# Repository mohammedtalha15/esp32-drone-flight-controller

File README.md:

# Custom ESP32 Devboard

It's a custom ESP32 devboard. It was designed to be a drone flight controller, but it's suitable for other projects as well.
I wanted to make this because I thought it was a good idea to try to design a drone with custom electronics. Turns out, electronics are hard, so I just made this.
It'll go on the drone when all the other parts are done. This project is being made for and funded by Hack Club's Highway program. 

This is my first circuit board by the way, hopefully I did a good job. I'm planning on designing my own brushless motor speed controller next, but I may just move on to the drone if that's too hard. 

## Features
- Integrated gyro and accelerometer (MPU-6050)
- Integrated magnetometer
- Voltage Regulator that drops drone battery voltage (14.8v) to 5v
- ESP32 Chip for processing, wifi, and bluetooth connectivity
- USB-C 2.0 port for programming and power supply
- Boot and Reset buttons
- A whole lotta GPIO pins

## BOM

| Item  | Usage | Source  | Price | Quantity |
| ----| ----|----|----|----|
| PCB | This is the project lol | JLCPCB | $77 | 5 (2 assembled)|

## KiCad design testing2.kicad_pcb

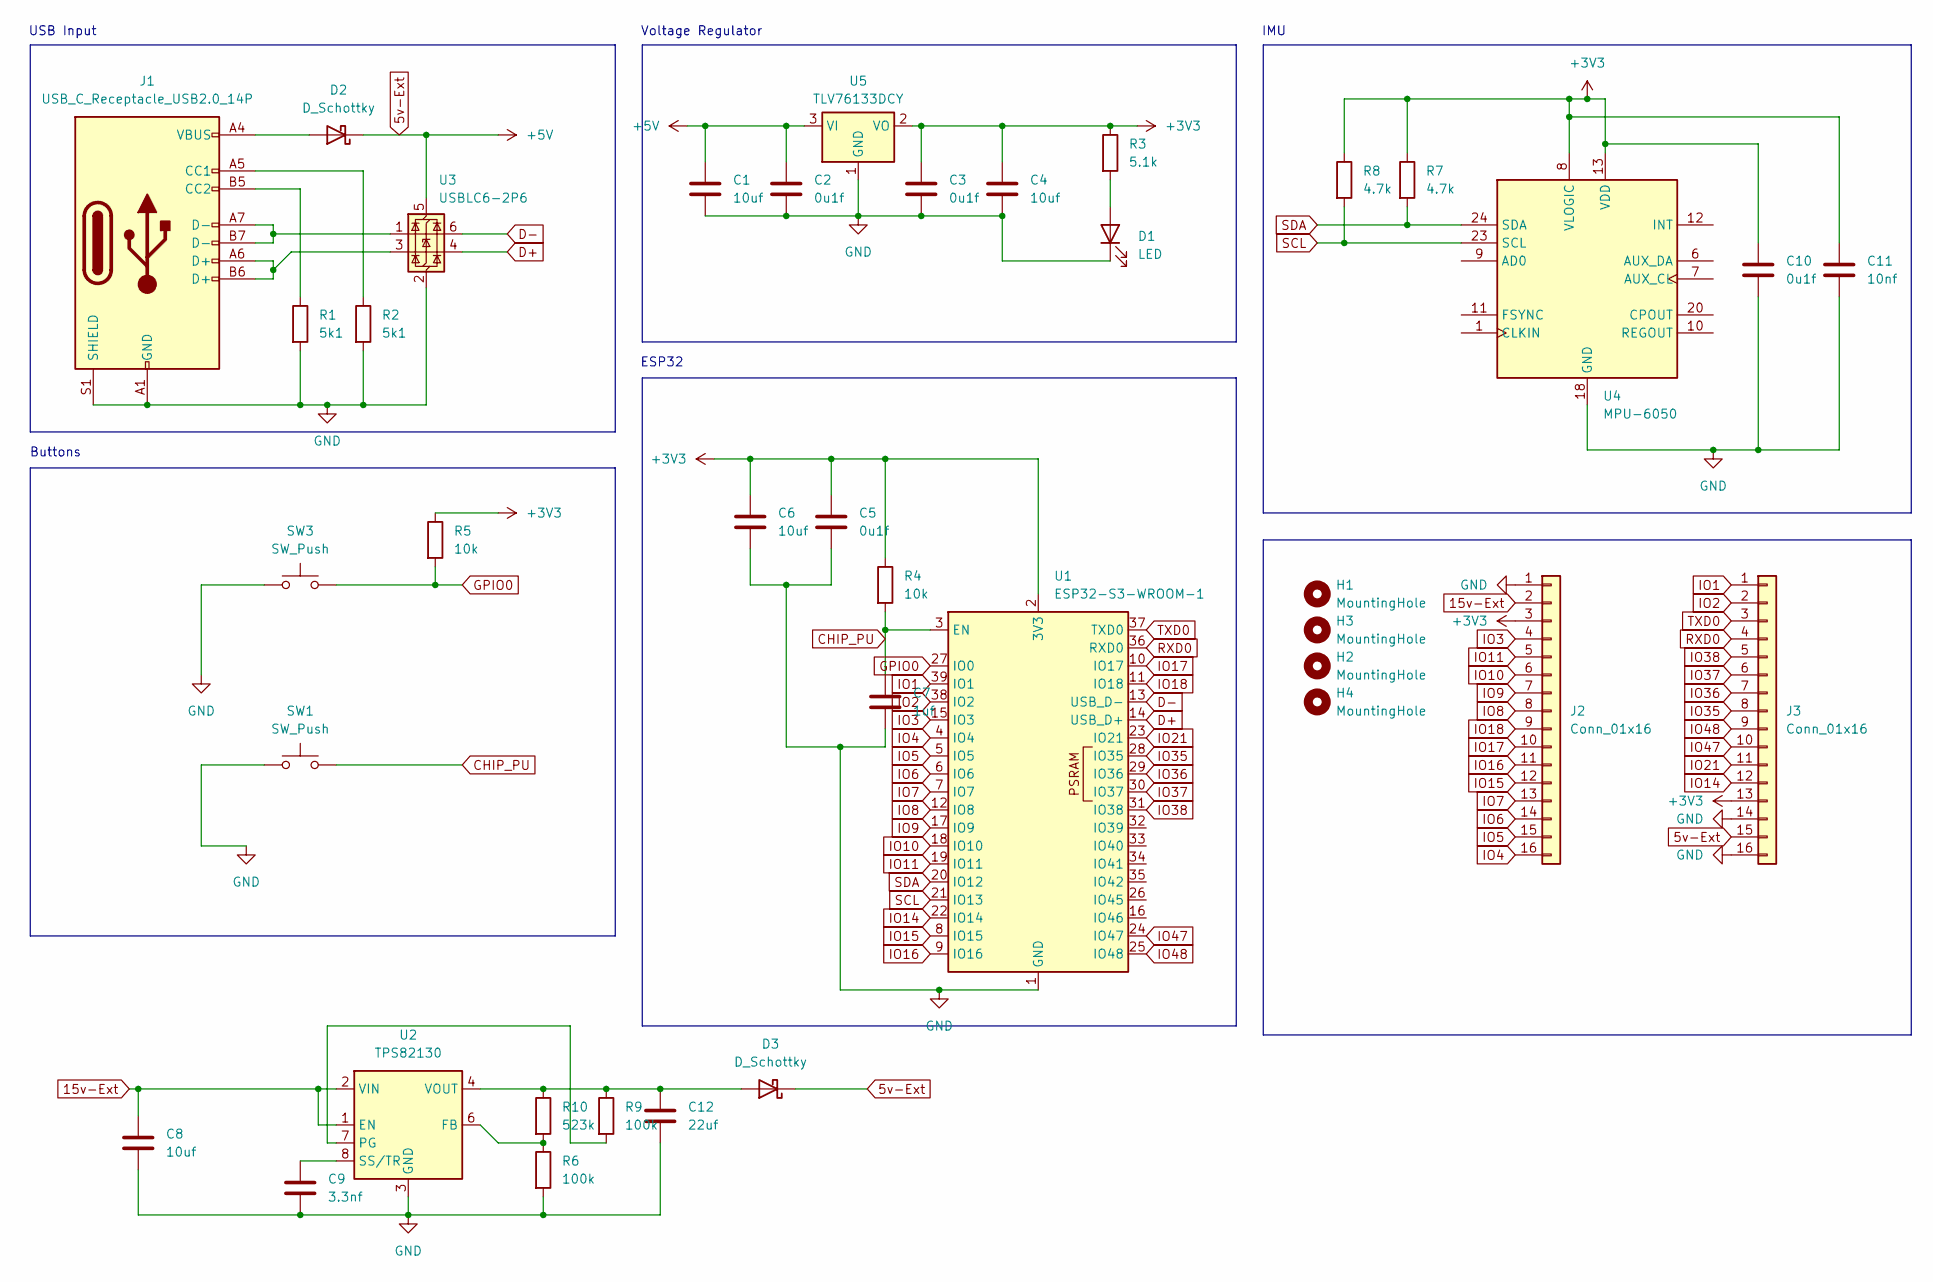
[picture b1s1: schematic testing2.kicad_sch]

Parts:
C1, C4, C6, C8: 10uf; C_0603_1608Metric
C2, C3, C5, C10: 0u1f; C_0201_0603Metric
C7: 1uf; C_0201_0603Metric
C9: 3.3nf; C_0201_0603Metric
C11: 10nf; C_0201_0603Metric
C12: 22uf; C_0603_1608Metric
D1: LED; LED_0603_1608Metric
D2, D3: D_Schottky; D_0603_1608Metric
H1, H2, H3, H4: MountingHole; MountingHole_2.2mm_M2
J1: USB_C_Receptacle_USB2.0_14P; USB_C_Receptacle_HCTL_HC-TYPE-C-16P-01A
J2, J3: Conn_01x16; PinHeader_1x16_P2.54mm_Vertical
R1, R2: 5k1; R_0201_0603Metric
R3: 5.1k; R_0201_0603Metric
R4, R5: 10k; R_0201_0603Metric
R6, R9: 100k; R_0201_0603Metric
R7, R8: 4.7k; R_0201_0603Metric
R10: 523k; R_0402_1005Metric
SW1, SW3: SW_Push; SW_Push_1P1T_NO_CK_KMR2
U1: ESP32-S3-WROOM-1
U2: TPS82130; Texas_SIL0008D_MicroSiP-8-1EP_2.8x3mm_P0.65mm_EP1.1x1.9mm_T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
U3: USBLC6-2P6; SOT-666
U4: MPU-6050; InvenSense_QFN-24_4x4mm_P0.5mm
U5: TLV76133DCY; SOT-223-3_TabPin2

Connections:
5v-Ext: C1.1, C2.1, D2.1 (K), D3.1 (K), J3.15, U3.5 (VBUS), U5.3 (VI)
15v-Ext: C8.1, J2.2, U2.1 (EN), U2.2 (VIN)
+3V3: C3.1, C4.1, C5.1, C6.1, C10.1, C11.1, J2.3, J3.13, R3.1, R4.1, R5.1, R7.1, R8.1, U1.2 (3V3), U4.8 (VLOGIC), U4.13 (VDD), U5.2 (VO)
CHIP_PU: C7.1, R4.2, SW1.2, U1.3 (EN)
D+: U1.14 (USB_D+), U3.4 (I/O2)
D-: U1.13 (USB_D-), U3.6 (I/O1)
GND: C1.2, C2.2, C3.2, C4.2, C5.2, C6.2, C7.2, C8.2, C9.2, C10.2, C11.2, C12.2, D1.1 (K), J1.A1 (GND), J1.A12 (GND), J1.B1 (GND), J1.B12 (GND), J1.S1 (SHIELD), J2.1, J3.14, J3.16, R1.2, R2.2, R6.2, SW1.1, SW3.1, U1.1 (GND), U1.40 (GND), U1.41 (GND), U2.3 (GND), U2.9 (GND), U3.2 (GND), U4.18 (GND), U5.1 (GND)
GPIO0: R5.2, SW3.2, U1.27 (IO0)
IO1: J3.1, U1.39 (IO1)
IO2: J3.2, U1.38 (IO2)
IO3: J2.4, U1.15 (IO3)
IO4: J2.16, U1.4 (IO4)
IO5: J2.15, U1.5 (IO5)
IO6: J2.14, U1.6 (IO6)
IO7: J2.13, U1.7 (IO7)
IO8: J2.8, U1.12 (IO8)
IO9: J2.7, U1.17 (IO9)
IO10: J2.6, U1.18 (IO10)
IO11: J2.5, U1.19 (IO11)
IO14: J3.12, U1.22 (IO14)
IO15: J2.12, U1.8 (IO15)
IO16: J2.11, U1.9 (IO16)
IO17: J2.10, U1.10 (IO17)
IO18: J2.9, U1.11 (IO18)
IO21: J3.11, U1.23 (IO21)
IO35: J3.8, U1.28 (IO35)
IO36: J3.7, U1.29 (IO36)
IO37: J3.6, U1.30 (IO37)
IO38: J3.5, U1.31 (IO38)
IO47: J3.10, U1.24 (IO47)
IO48: J3.9, U1.25 (IO48)
unnamed: D1.2 (A), R3.2
unnamed: D2.2 (A), J1.A4 (VBUS), J1.A9 (VBUS), J1.B4 (VBUS), J1.B9 (VBUS)
unnamed: C12.1, D3.2 (A), R9.1, R10.1, U2.4 (VOUT), U2.5 (VOUT)
unnamed: J1.A5 (CC1), R2.1
unnamed: J1.B5 (CC2), R1.1
unnamed: J1.A6 (D+), J1.B6 (D+), U3.3 (I/O2)
unnamed: J1.A7 (D-), J1.B7 (D-), U3.1 (I/O1)
unnamed: R6.1, R10.2, U2.6 (FB)
unnamed: R9.2, U2.7 (PG)
unnamed: C9.1, U2.8 (SS/TR)
RXD0: J3.4, U1.36 (RXD0)
SCL: R8.2, U1.21 (IO13), U4.23 (SCL)
SDA: R7.2, U1.20 (IO12), U4.24 (SDA)
TXD0: J3.3, U1.37 (TXD0)

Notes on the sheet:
IMU
Voltage Regulator
Buttons
ESP32
USB Input

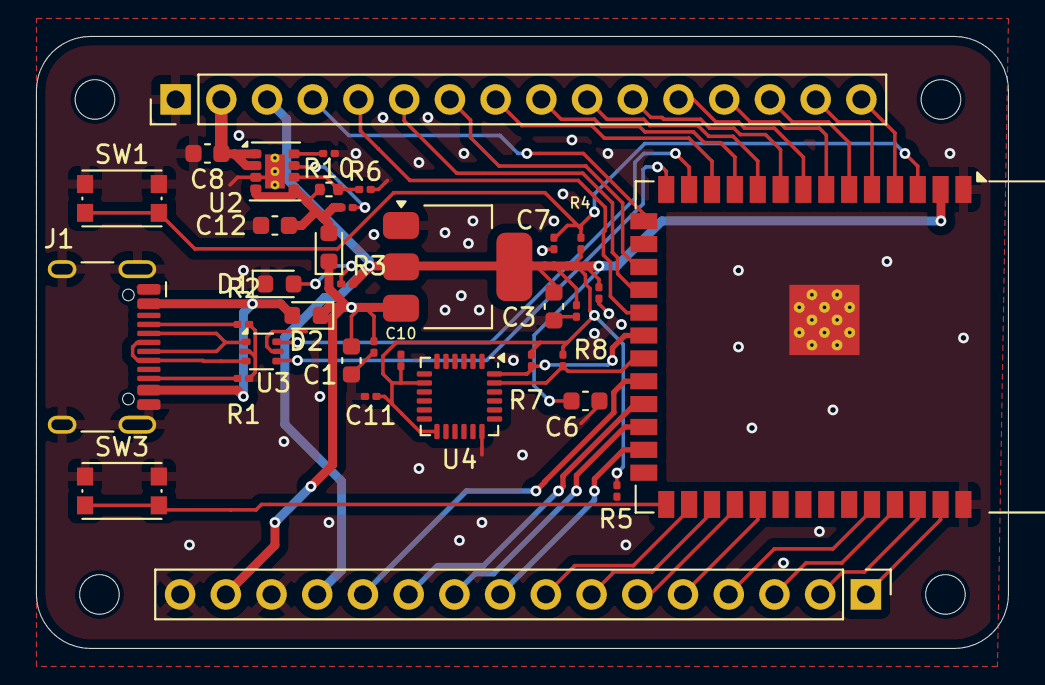
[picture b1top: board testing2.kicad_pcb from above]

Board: 2 copper layers, 54.0 x 34.0 mm, 39 parts (0 on the bottom side), 45 nets.

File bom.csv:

Designator,Footprint,Quantity,Value,LCSC Part #
"C1, C4, C6, C8",0603,4,10uf,
"C10, C2, C3, C5",0201,4,0u1f,
C11,0201,1,10nf,
C12,0603,1,22uf,
C7,0201,1,1uf,
C9,0201,1,3.3nf,
D1,0603,1,LED,
"D2, D3",0603,2,D_Schottky,
J1,USB_C_Receptacle_HCTL_HC-TYPE-C-16P-01A,1,USB_C_Receptacle_USB2.0_14P,
"J2, J3",PinHeader_1x16_P2.54mm_Vertical,2,Conn_01x16,
"R1, R2",0201,2,5k1,
R10,0402,1,523k,
R3,0201,1,5.1k,
"R4, R5",0201,2,10k,
"R6, R9",0201,2,100k,
"R7, R8",0201,2,4.7k,
"SW1, SW3",SW_Push_1P1T_NO_CK_KMR2,2,SW_Push,
U1,ESP32-S3-WROOM-1,1,ESP32-S3-WROOM-1,
U2,Texas_SIL0008D_MicroSiP-8-1EP_2.8x3mm_P0.65mm_EP1.1x1.9mm_ThermalVias,1,TPS82130,
U3,SOT-666,1,USBLC6-2P6,
U4,InvenSense_QFN-24_4x4mm_P0.5mm,1,MPU-6050,
U5,SOT-223-3_TabPin2,1,TLV76133DCY,
